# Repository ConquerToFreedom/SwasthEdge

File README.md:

# SwasthEdge
Low-cost self-diagnosing edge controller for industrial sensor reliability

## Overview
- Monitors sensor, electrical, and MCU health
- Fuses evidence into a fault-confidence score
- On-device TinyML on STM32F446RE
- Local response: Normal → Warning → Degraded → Critical
- Physical fault injection validation

## Repository Structure
- `/firmware` – STM32 firmware
- `/hardware` – KiCad schematic, PCB layout, BOM
- `/ml` – Data, notebooks, models
- `/docs` – Architecture, validation protocol, reports
- `/ppt` – Presentation slides
- `/video` – Demo video links

## Documentation
- [System Architecture](docs/architecture/Architecture.md)
- [Architecture Diagram (PDF)](docs/architecture/SwasthEdge_Architecture.pdf)
- [Complete Pin Mapping (Markdown)](docs/architecture/PinMapping.md)
- [Pin Mapping (CSV for Excel)](docs/architecture/PinMapping.csv)

## 📂 Project Media & Sources
- [Google Drive Folder for Image Sources](https://drive.google.com/drive/folders/1q7pAoYTXLVP09OUnn3g1jxPzuWNZ1AVV)

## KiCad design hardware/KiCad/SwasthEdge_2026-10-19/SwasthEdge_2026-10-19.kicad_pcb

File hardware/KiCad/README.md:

# SwasthEdge KiCad project

Open `SwasthEdge/SwasthEdge.kicad_pro` with KiCad 10.

## Current project files

- `SwasthEdge/SwasthEdge.kicad_sch` — current schematic. The supplied October 22, 2026 file matches this repository file byte-for-byte.
- `SwasthEdge/SwasthEdge.kicad_pcb` — updated with the supplied `powermod_experimental_all_footprints_routed (2).kicad_pcb`, renamed to match the project.
- `SwasthEdge/SwasthEdge.kicad_pro` — existing KiCad project settings.

## Related artifacts and validation

`SwasthEdge/SwasthEdge.net`, `SwasthEdge/SwasthEdge_footprint_report.txt`, and `SwasthEdge/SwasthEdge_board_preview.png` are from the earlier October 19 snapshot and were not regenerated for the updated board. Do not use them to validate the October 22 PCB.

The PCB was supplied with “routed” in its filename, but this update does not establish that routing passes KiCad DRC or that the schematic passes ERC. Run ERC and DRC in KiCad before treating the board as fabrication-ready.

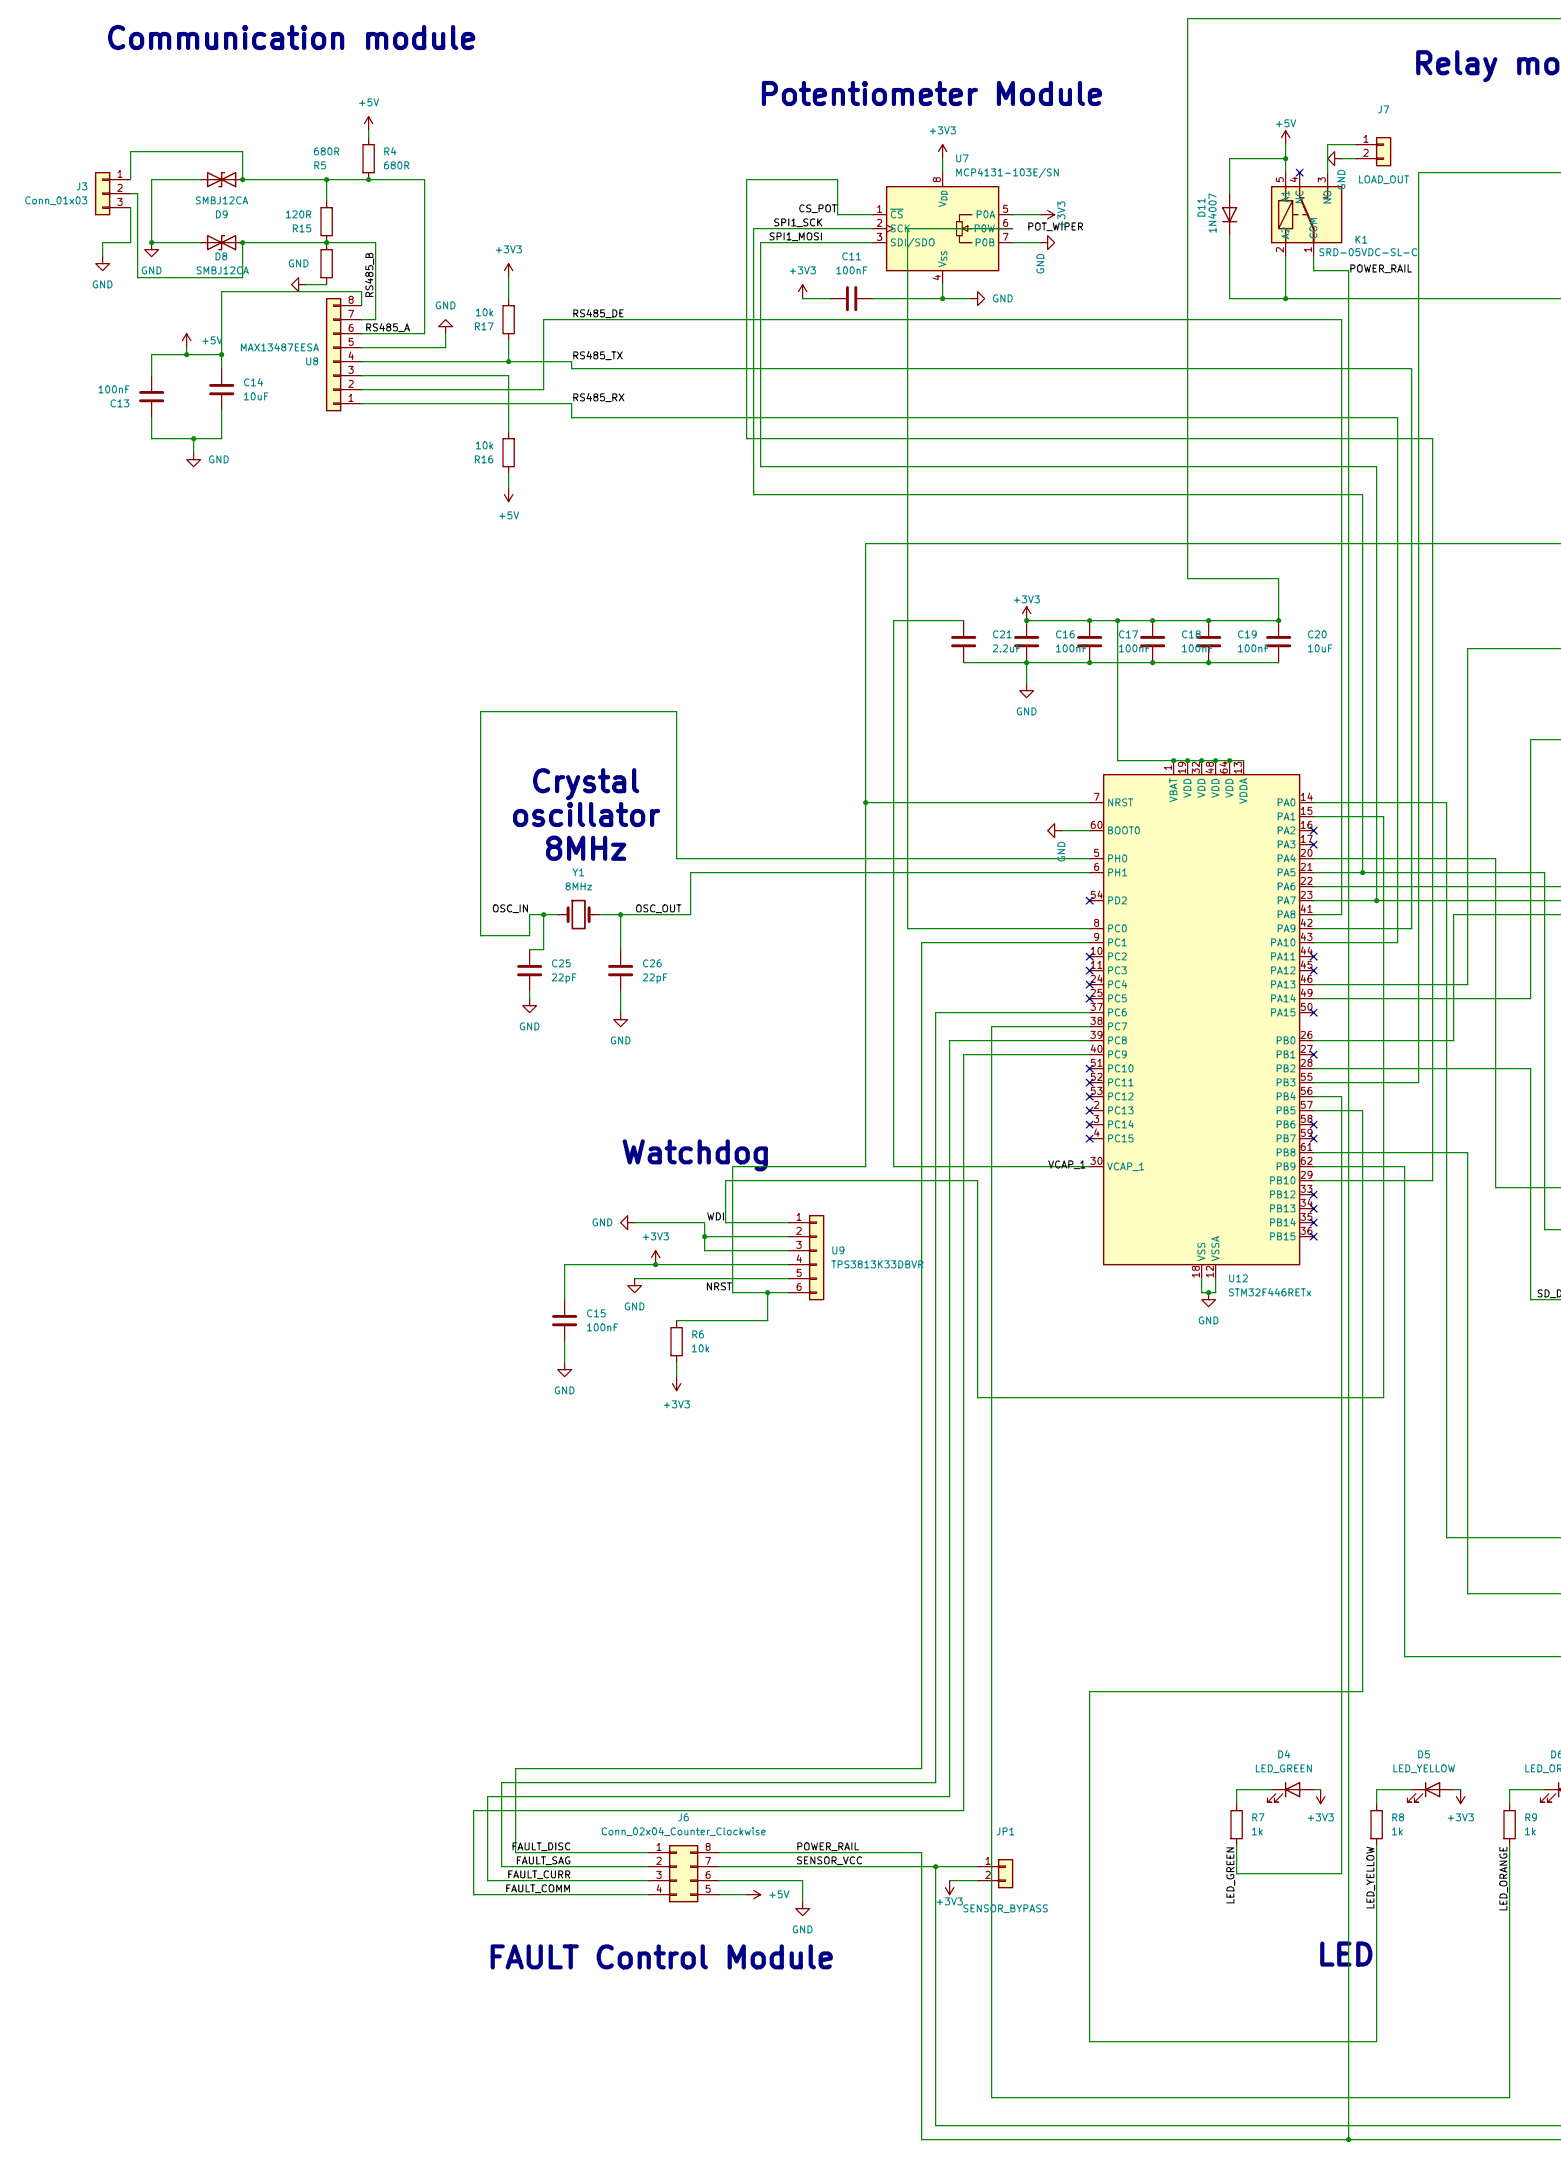
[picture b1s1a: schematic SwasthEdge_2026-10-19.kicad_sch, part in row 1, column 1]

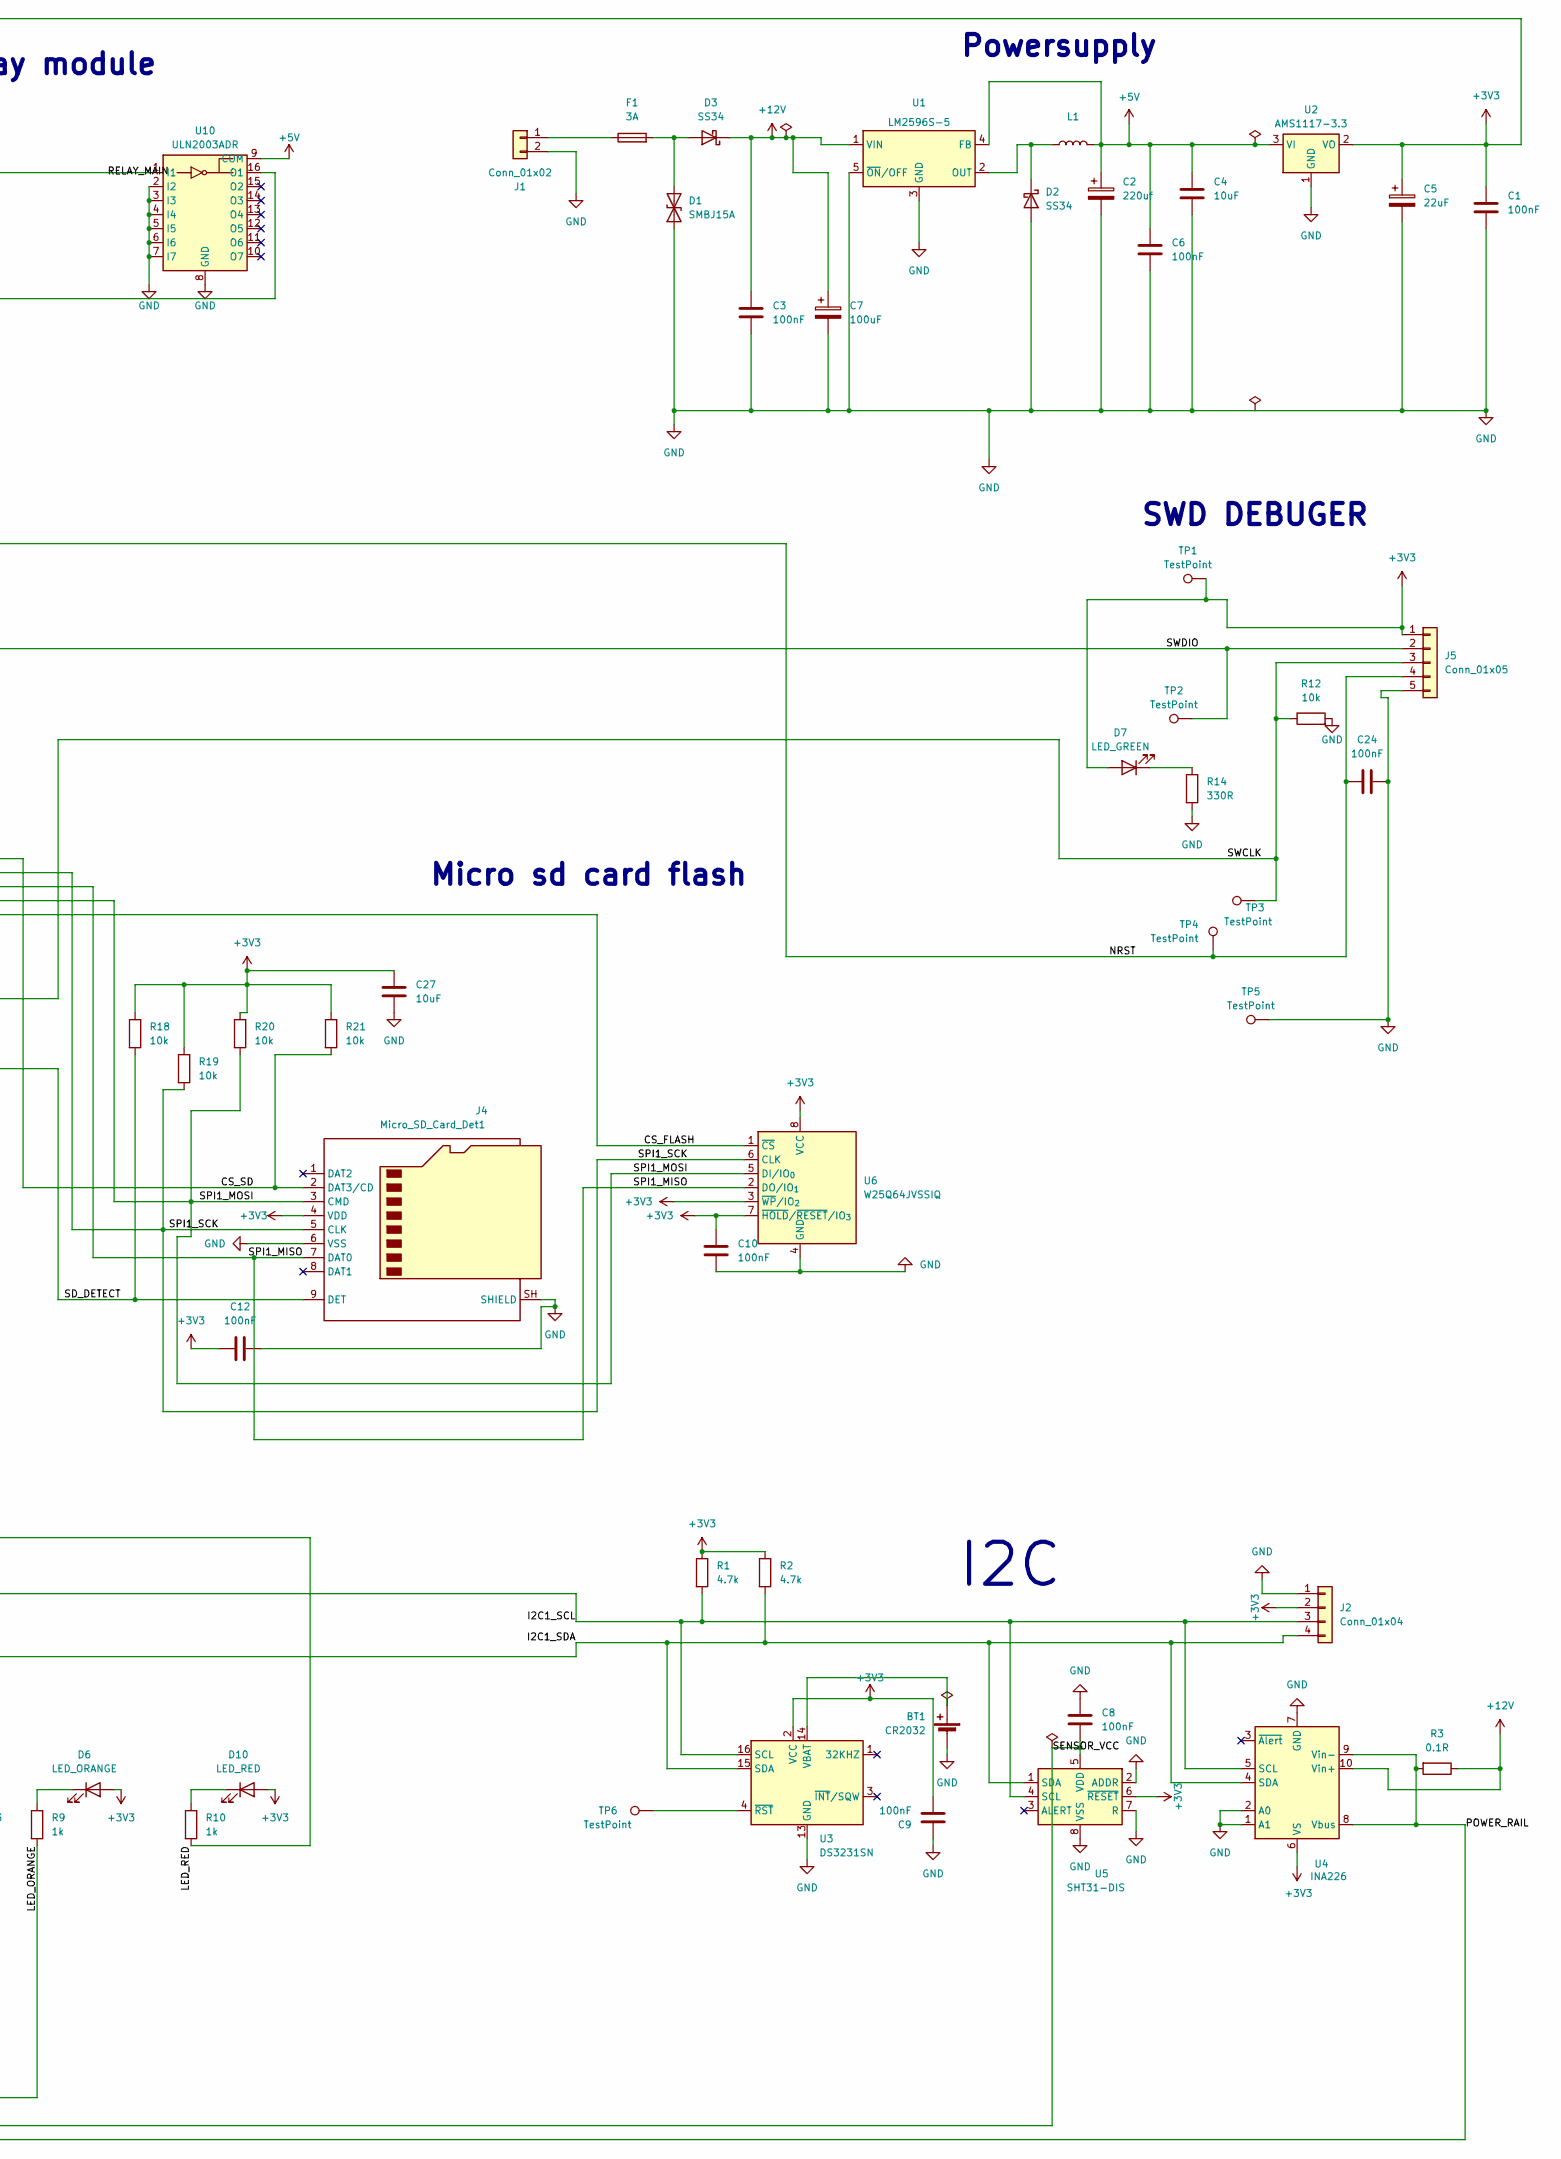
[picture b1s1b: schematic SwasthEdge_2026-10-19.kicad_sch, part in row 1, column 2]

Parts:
BT1: CR2032; BatteryHolder_Keystone_3000_1xCR2032
C1, C3, C6, C8, C9, C10, C11, C12, C13, C15, C16, C17, C18, C19, C24: 100nF; C_0805_2012Metric
C2: 220uf; CP_Radial_D8.0mm_P3.50mm
C4, C14, C20, C27: 10uF; C_0805_2012Metric
C5: 22uF; CP_EIA-3528-21_Kemet-B
C7: 100uF; CP_Radial_D8.0mm_P3.50mm
C21: 2.2uF; C_0805_2012Metric
C25, C26: 22pF; C_0805_2012Metric
D1: SMBJ15A; D_SMB
D2, D3: SS34; D_SMC
D4, D7: LED_GREEN; LED_0805_2012Metric
D5: LED_YELLOW; LED_0805_2012Metric
D6: LED_ORANGE; LED_0805_2012Metric
D8, D9: SMBJ12CA; D_SMB
D10: LED_RED; LED_0805_2012Metric
D11: 1N4007; D_DO-41_SOD81_P7.62mm_Horizontal
F1: 3A; Fuse_1206_3216Metric
J1: Conn_01x02; PinHeader_1x02_P2.54mm_Vertical
J2: Conn_01x04; PinHeader_1x04_P2.54mm_Vertical
J3: Conn_01x03; PinHeader_1x03_P2.54mm_Vertical
J4: Micro_SD_Card_Det1; microSD_HC_Hirose_DM3AT-SF-PEJM5
J5: Conn_01x05; PinHeader_1x05_P2.54mm_Vertical
J6: Conn_02x04_Counter_Clockwise; PinHeader_2x04_P2.54mm_Vertical
J7: LOAD_OUT; TerminalBlock_Phoenix_MKDS-1,5-2-5.08_1x02_P5.08mm_Horizont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
JP1: SENSOR_BYPASS; PinHeader_1x02_P2.54mm_Vertical
K1: SRD-05VDC-SL-C; Relay_SPDT_SANYOU_SRD_Series_Form_C
L1: 33µH; L_10.4x10.4_H4.8
R1, R2: 4.7k; R_0805_2012Metric
R3: 0.1R; R_2512_6332Metric
R4, R5: 680R; R_0805_2012Metric
R6, R12, R16, R17, R18, R19, R20, R21: 10k; R_0805_2012Metric
R7, R8, R9, R10: 1k; R_0805_2012Metric
R14: 330R; R_0805_2012Metric
R15: 120R; R_0805_2012Metric
TP1, TP2, TP3, TP4, TP5, TP6: TestPoint; TestPoint_Pad_D1.0mm
U1: LM2596S-5; TO-263-5_TabPin3
U2: AMS1117-3.3; SOT-223-3_TabPin2
U3: DS3231SN; SOIC-16W_7.5x10.3mm_P1.27mm
U4: INA226; TSSOP-10_3x3mm_P0.5mm
U5: SHT31-DIS; Sensirion_DFN-8-1EP_2.5x2.5mm_P0.5mm_EP1.1x1.7mm
U6: W25Q64JVSSIQ; SOIC-8_5.3x5.3mm_P1.27mm
U7: MCP4131-103E/SN; SOIC-8_3.9x4.9mm_P1.27mm
U8: MAX13487EESA; SOIC-8_3.9x4.9mm_P1.27mm
U9: TPS3813K33DBVR; SOT-23-6
U10: ULN2003ADR; SOIC-16_3.9x9.9mm_P1.27mm
U12: STM32F446RETx; LQFP-64_10x10mm_P0.5mm
Y1: 8MHz; Crystal_HC49-U_Vertical

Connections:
+3V3: C1.1, C5.1, C9.2, C10.1, C11.1, C12.1, C15.1, C16.1, C17.1, C18.1, C19.1, C20.1, C27.1, D4.2 (A), D5.2 (A), D6.2 (A), D7.2 (A), D10.2 (A), J2.2, J4.4 (VDD), J5.1, JP1.2, R1.1, R2.1, R6.2, R17.2, R18.1, R19.1, R20.1, R21.1, TP1.1 (1_1), U2.2 (VO), U3.2 (VCC), U4.6 (VS), U5.6 (~RESET), U6.3 (~WP/IO_{2}), U6.7 (~HOLD/~RESET/IO_{3}), U6.8 (VCC), U7.5 (P0A), U7.8 (V_{DD}), U9.4, U12.1 (VBAT), U12.13 (VDDA), U12.19 (VDD), U12.32 (VDD), U12.48 (VDD), U12.64 (VDD)
+5V: C2.1, C4.1, C6.1, C13.2, C14.1, D11.2 (A), J6.5, K1.5 (A1), L1.2, R4.1, R16.1, U1.4 (FB), U2.3 (VI), U8.8, U10.9 (COM)
+12V: C3.1, C7.1, D3.1 (K), R3.1, U1.1 (VIN), U4.10 (Vin+)
/CS_FLASH: U6.1 (~CS), U12.26 (PB0)
/CS_POT: U7.1 (~CS), U12.29 (PB10)
/CS_SD: J4.2 (DAT3/CD), R21.2, U12.20 (PA4)
/FAULT_COMM: J6.4, U12.40 (PC9)
/FAULT_CURR: J6.3, U12.39 (PC8)
/FAULT_DISC: J6.1, U12.9 (PC1)
/FAULT_SAG: J6.2, U12.37 (PC6)
/I2C1_SCL: J2.3, R1.2, U3.16 (SCL), U4.5 (SCL), U5.4 (SCL), U12.61 (PB8)
/I2C1_SDA: J2.4, R2.2, U3.15 (SDA), U4.4 (SDA), U5.1 (SDA), U12.62 (PB9)
/LED_GREEN: R7.2, U12.56 (PB4)
/LED_ORANGE: R9.2, U12.38 (PC7)
/LED_RED: R10.2, U12.14 (PA0)
/LED_YELLOW: R8.2, U12.57 (PB5)
/NRST: C24.2, J5.4, R6.1, TP4.1 (1_1), U9.6, U12.7 (NRST)
/OSC_IN: C25.1, U12.5 (PH0), Y1.1
/OSC_OUT: C26.1, U12.6 (PH1), Y1.2
/POWER_RAIL: J6.8, K1.1 (COM), R3.2, U4.8 (Vbus), U4.9 (Vin-)
/RELAY_MAIN: U10.1 (I1), U12.55 (PB3)
/RS485_A: D9.1 (A1), J3.1, R4.2, R15.2, U8.6
/RS485_B: D8.1 (A1), J3.2, R5.1, R15.1, U8.7
/RS485_DE: U8.2, U12.41 (PA8)
/RS485_RX: U8.1, U12.43 (PA10)
/RS485_TX: R17.1, U8.4, U12.42 (PA9)
/SD_DETECT: J4.9 (DET), R18.2, U12.28 (PB2)
/SENSOR_VCC: C8.1, J6.7, JP1.1, U5.5 (VDD)
/SPI1_MISO: J4.7 (DAT0), U6.2 (DO/IO_{1}), U12.22 (PA6)
/SPI1_MOSI: J4.3 (CMD), R20.2, U6.5 (DI/IO_{0}), U7.3 (SDI/SDO), U12.23 (PA7)
/SPI1_SCK: J4.5 (CLK), R19.2, U6.6 (CLK), U7.2 (SCK), U12.21 (PA5)
/SWCLK: J5.3, R12.1, TP3.1 (1_1), U12.49 (PA14)
/SWDIO: J5.2, TP2.1 (1_1), U12.46 (PA13)
/VCAP_1: C21.1, U12.30 (VCAP_1)
/WDI: U9.1, U12.15 (PA1)
GND: BT1.2, C1.2, C2.2, C3.2, C4.2, C5.2, C6.2, C7.2, C8.2, C9.1, C10.2, C11.2, C12.2, C13.1, C14.2, C15.2, C16.2, C17.2, C18.2, C19.2, C20.2, C21.2, C24.1, C25.2, C26.2, C27.2, D1.1 (A1), D2.2 (A), D8.2 (A2), D9.2 (A2), J1.2, J2.1, J3.3, J4.6 (VSS), J4.SH (SHIELD), J5.5, J6.6, J7.2, R5.2, R12.2, R14.2, TP5.1 (1_1), U1.3 (GND), U1.5 (~ON/OFF), U2.1 (GND), U3.5 (GND), U3.6 (GND), U3.7 (GND), U3.8 (GND), U3.9 (GND), U3.10 (GND), U3.11 (GND), U3.12 (GND), U3.13 (GND), U4.1 (A1), U4.2 (A0), U4.7 (GND), U5.2 (ADDR), U5.7 (R), U5.8 (VSS), U5.9 (VSS), U6.4 (GND), U7.4 (V_{SS}), U7.7 (P0B), U8.5, U9.2, U9.3, U9.5, U10.2 (I2), U10.3 (I3), U10.4 (I4), U10.5 (I5), U10.6 (I6), U10.7 (I7), U10.8 (GND), U12.12 (VSSA), U12.18 (VSS), U12.31 (VSS), U12.47 (VSS), U12.60 (BOOT0), U12.63 (VSS); also elsewhere on the board
unnamed: BT1.1, U3.14 (VBAT)
unnamed: D1.2 (A2), D3.2 (A), F1.2
unnamed: D2.1 (K), L1.1, U1.2 (OUT)
unnamed: D4.1 (K), R7.1
unnamed: D5.1 (K), R8.1
unnamed: D6.1 (K), R9.1
unnamed: D7.1 (K), R14.1
unnamed: D10.1 (K), R10.1
unnamed: D11.1 (K), K1.2 (A2), U10.16 (O1)
unnamed: F1.1, J1.1
unnamed: J7.1, K1.3 (NO)
unnamed: TP6.1 (1_1), U3.4 (~RST)
unnamed: R16.2, U8.3
unnamed: U7.6 (P0W), U12.8 (PC0)

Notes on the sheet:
Micro sd card flash
SWD DEBUGER
Communication module
Crystal oscillator 8MHz
Relay module
I2C
LED
Watchdog
FAULT Control Module
Powersupply
Potentiometer Module

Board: 2 copper layers, 89 parts (0 on the bottom side), 50 nets, no tracks yet.

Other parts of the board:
H1, H2, H3, H4: MountingHole_Pad; MountingHole_3.2mm_M3_Pad

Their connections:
GND: H1.1, H2.1, H3.1, H4.1; also elsewhere on the board

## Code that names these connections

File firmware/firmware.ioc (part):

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Mcu.Name=STM32F446R(C-E)Tx
Mcu.Package=LQFP64
Mcu.UserName=STM32F446RETx
PA0-WKUP.GPIOParameters=GPIO_Label
PA0-WKUP.GPIO_Label=LED_RED
PA0-WKUP.Signal=GPIO_Output
PA1.GPIOParameters=GPIO_Label
PA1.GPIO_Label=WDI
PA1.Signal=GPIO_Output
PA10.Mode=Asynchronous
PA10.Signal=USART1_RX
PA13.Mode=Serial_Wire
PA13.Signal=SYS_JTMS-SWDIO
PA14.Mode=Serial_Wire
PA14.Signal=SYS_JTCK-SWCLK
PA2.Mode=Asynchronous
PA2.Signal=USART2_TX
PA3.Mode=Asynchronous
PA3.Signal=USART2_RX
PA4.GPIOParameters=GPIO_Label
PA4.GPIO_Label=CS_SD
PA4.Signal=GPIO_Output
PA5.Mode=Full_Duplex_Master
PA5.Signal=SPI1_SCK
PA6.Mode=Full_Duplex_Master
PA6.Signal=SPI1_MISO
PA7.Mode=Full_Duplex_Master
PA7.Signal=SPI1_MOSI
PA8.GPIOParameters=GPIO_Label
PA8.GPIO_Label=RS485_DE
PA8.Signal=GPIO_Output
PA9.Mode=Asynchronous
PA9.Signal=USART1_TX
PB0.GPIOParameters=GPIO_Label
PB0.GPIO_Label=CS_FLASH
PB0.Signal=GPIO_Output
PB10.GPIOParameters=GPIO_Label
PB10.GPIO_Label=CS_POT
PB10.Signal=GPIO_Output
PB2.GPIOParameters=GPIO_Label
PB2.GPIO_Label=SD_DETECT
PB2.Signal=GPIO_Input
PB3.GPIOParameters=GPIO_Label
PB3.GPIO_Label=RELAY_MAIN
PB3.Signal=GPIO_Output
PB4.GPIOParameters=GPIO_Label
PB4.GPIO_Label=LED_GREEN
PB4.Signal=GPIO_Output
PB5.GPIOParameters=GPIO_Label
PB5.GPIO_Label=LED_YELLOW
PB5.Signal=GPIO_Output
PB6.GPIOParameters=GPIO_Label
PB6.GPIO_Label=RELAY_FEEDBACK
PB6.Signal=GPIO_Output
PB8.Mode=I2C
PB8.Signal=I2C1_SCL
PB9.Mode=I2C
PB9.Signal=I2C1_SDA
PC1.GPIOParameters=GPIO_Label
PC1.GPIO_Label=FAULT_DISC
PC1.Signal=GPIO_Output
PC6.Signal=S_TIM3_CH1
PC7.GPIOParameters=GPIO_Label
PC7.GPIO_Label=LED_ORANGE
PC7.Signal=GPIO_Output
PC8.GPIOParameters=GPIO_Label
PC8.GPIO_Label=FAULT_CURR
PC8.Signal=GPIO_Output
PC9.GPIOParameters=GPIO_Label
PC9.GPIO_Label=FAULT_COMM
PC9.Signal=GPIO_Output
PH0-OSC_IN.Mode=HSE-External-Oscillator
PH0-OSC_IN.Signal=RCC_OSC_IN
PH1-OSC_OUT.Mode=HSE-External-Oscillator
PH1-OSC_OUT.Signal=RCC_OSC_OUT
RCC.HSE_VALUE=8000000
RCC.SYSCLKFreq_VALUE=180000000
RCC.SYSCLKSource=RCC_SYSCLKSOURCE_PLLCLK
board=custom
